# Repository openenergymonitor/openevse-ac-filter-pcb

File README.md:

# openevse-ac-filter-pcb

AC filter for the 240V AC input to OpenEVSE controller. Used to filter the switching noise of the onboard AC-DC SMPS (MINMAX ABF-04S12)

## BOM

- 1 x 47 mH Schaffner RN Common Mode Choke (RN214-0.3-02-47M) or (Horizontal RN114-0.3-02-47M)
- 2 x Safety capacitors X1/X2/Y2 10nF (DE2F3KY103MA3BM02F)
- 1 x 5x20mm fuse holder

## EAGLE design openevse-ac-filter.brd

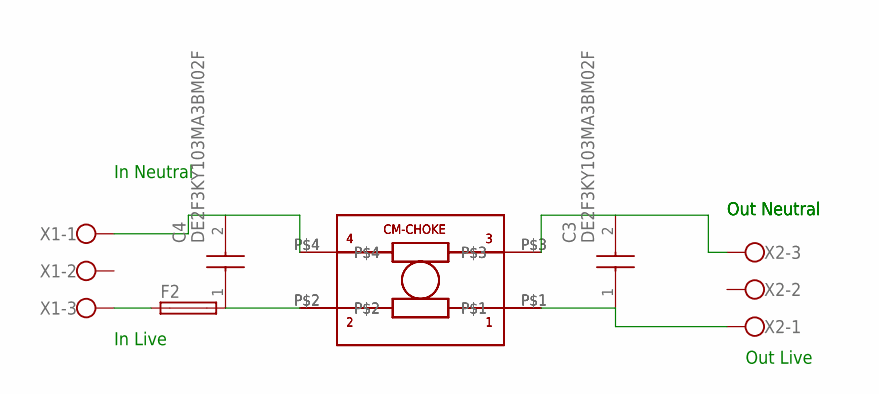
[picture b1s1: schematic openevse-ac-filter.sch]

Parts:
C3, C4: DE2F3KY103MA3BM02F
F2: GSH15
U$1: 47mH; RN114-0.3-02-47M
U$2: RN214-0.3-02-47M
X1, X2: W237-103

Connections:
unnamed: C3.2, U$1.P$3, U$2.P$3, X2.3
unnamed: F2.1, X1.3
unnamed: C4.2, U$1.P$4, U$2.P$4, X1.1
unnamed: C3.1, U$1.P$1, U$2.P$1, X2.1
unnamed: C4.1, F2.2, U$1.P$2, U$2.P$2

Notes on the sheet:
In Neutral
Out Neutral
In Live
Out Live

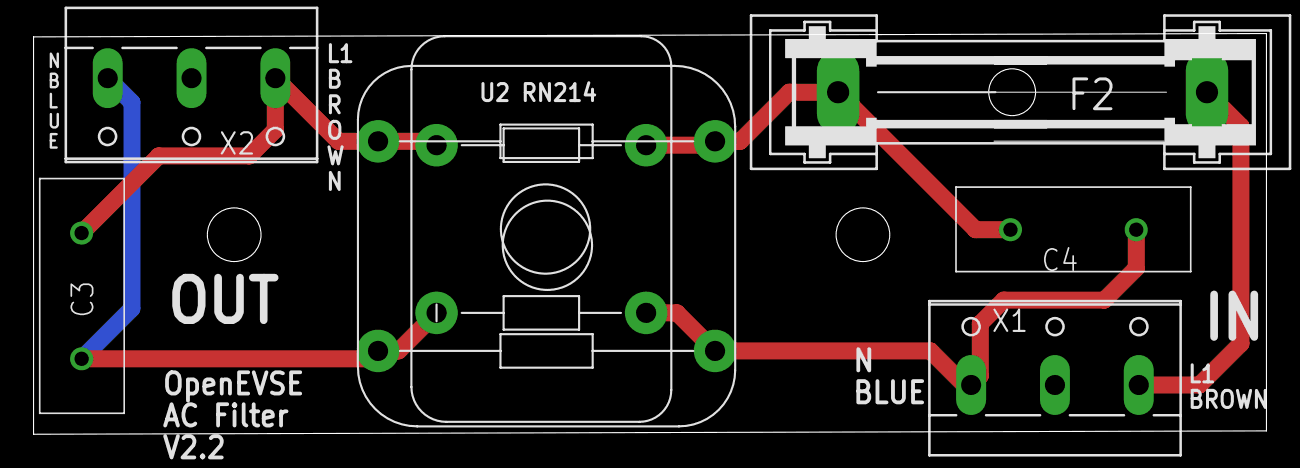
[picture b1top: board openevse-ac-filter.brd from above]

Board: 2 copper layers, 73.5 x 23.9 mm, 7 parts (0 on the bottom side), 5 nets.

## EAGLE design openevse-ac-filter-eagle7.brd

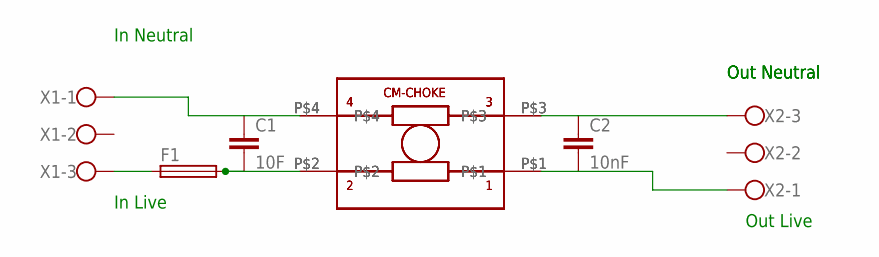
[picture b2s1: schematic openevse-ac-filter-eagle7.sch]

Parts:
C1: 10F; C5B2.5
C2: 10nF; C5B2.5
F1: GSH15
U$1: 47mH; RN114-0.3-02-47M
U$2: RN214-0.3-02-47M
X1, X2: W237-103

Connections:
unnamed: C1.1, U$1.P$4, U$2.P$4, X1.1
unnamed: C1.2, F1.2, U$1.P$2, U$2.P$2
unnamed: C2.1, U$1.P$3, U$2.P$3, X2.3
unnamed: C2.2, U$1.P$1, U$2.P$1, X2.1
unnamed: F1.1, X1.3

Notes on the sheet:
In Neutral
Out Neutral
In Live
Out Live

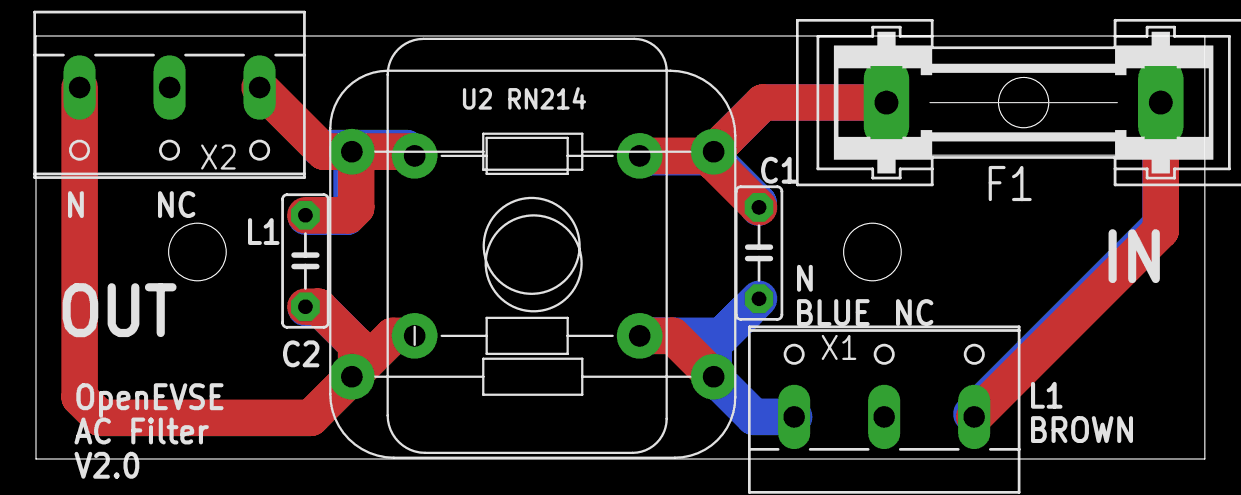
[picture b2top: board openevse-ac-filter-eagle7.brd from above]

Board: 2 copper layers, 64.9 x 23.5 mm, 7 parts (0 on the bottom side), 5 nets.

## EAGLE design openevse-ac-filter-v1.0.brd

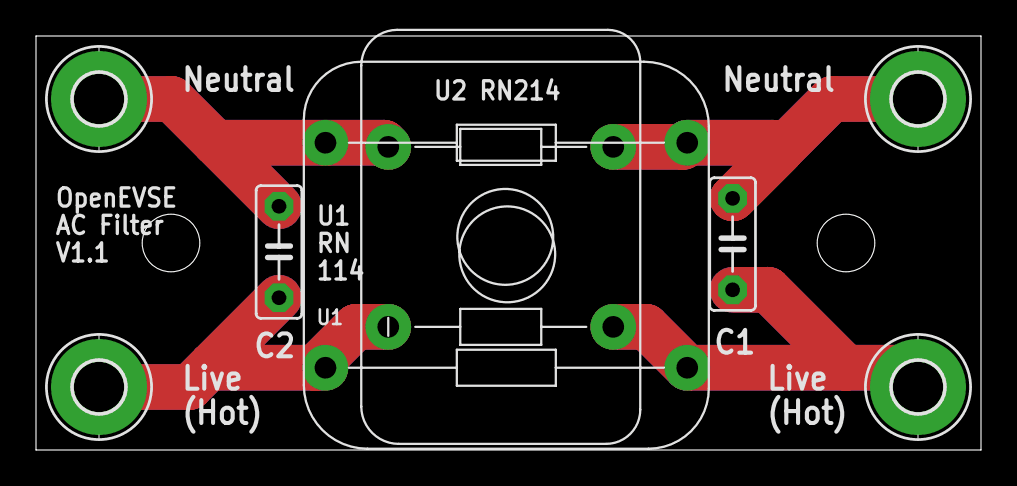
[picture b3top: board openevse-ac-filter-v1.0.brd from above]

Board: 2 copper layers, 52.5 x 23.0 mm, 8 parts (0 on the bottom side), 4 nets.

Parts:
C1: 10F; C5B2.5
C2: 10nF; C5B2.5
H2, H3, H4, H5: MOUNT-PAD-ROUND2.8; 2,8-PAD
U$1: 47mH; RN114-0.3-02-47M
U$2: RN214-0.3-02-47M

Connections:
unnamed: C1.1, H5.B2,8, U$1.P$4, U$2.P$4
unnamed: C1.2, H2.B2,8, U$1.P$2, U$2.P$2
unnamed: C2.1, H3.B2,8, U$1.P$3, U$2.P$3
unnamed: C2.2, H4.B2,8, U$1.P$1, U$2.P$1

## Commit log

2018-03-16 first commit V1.0
2018-03-16 update library drill & pad
2018-03-16 V1.2 increase pad and hole size
2018-03-16 add images
2018-03-18 add photo rename
2018-04-05 fix filname
2018-04-05 V1.2 decrease hole size
2018-04-05 smaller dimensions
2018-04-05 new export
2019-05-29 V1.3 with terminal blocks
2019-10-18 add v1.4
2019-10-18 restore schematic
2020-04-20 bump version v2.0
2020-04-20 update BOM
2020-04-27 bump v2.1
2022-08-02 v2.2
